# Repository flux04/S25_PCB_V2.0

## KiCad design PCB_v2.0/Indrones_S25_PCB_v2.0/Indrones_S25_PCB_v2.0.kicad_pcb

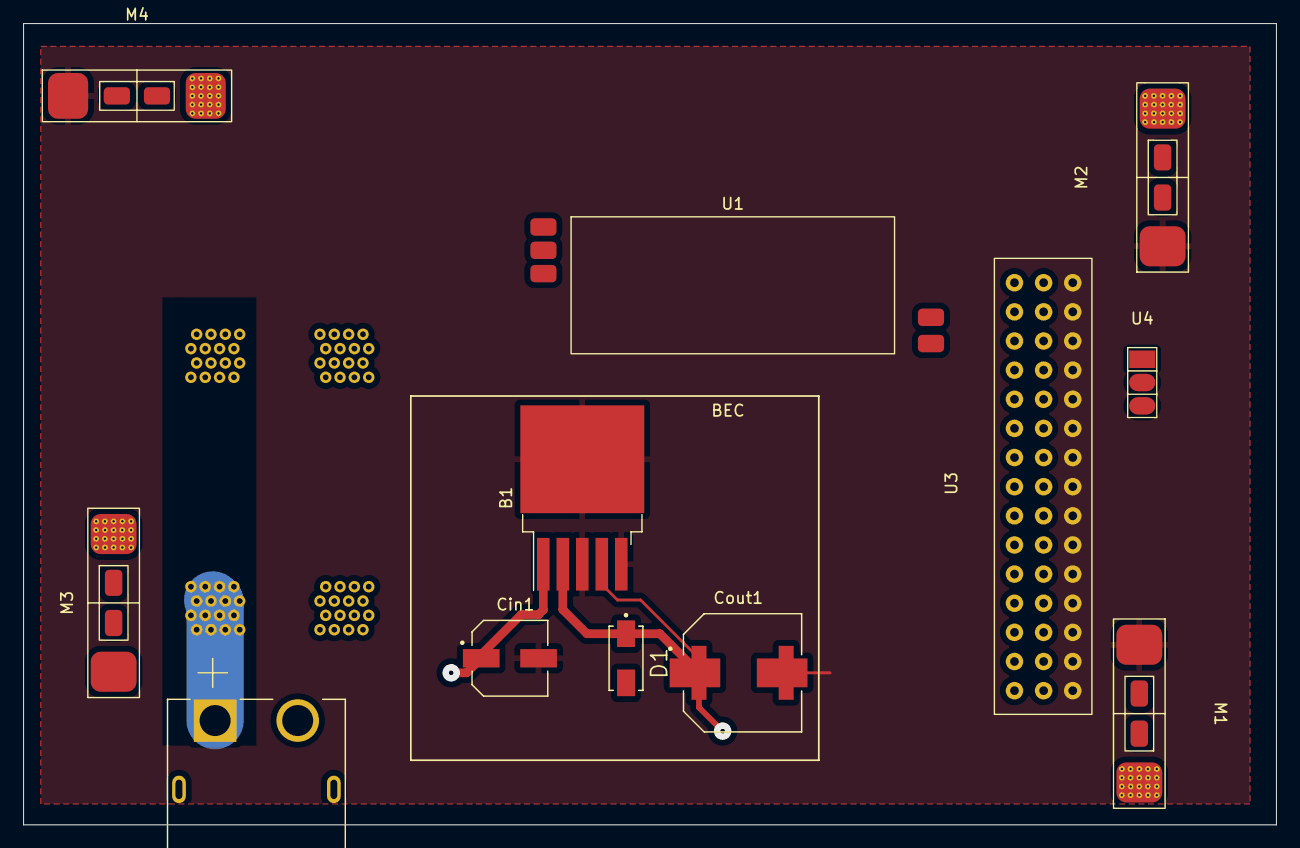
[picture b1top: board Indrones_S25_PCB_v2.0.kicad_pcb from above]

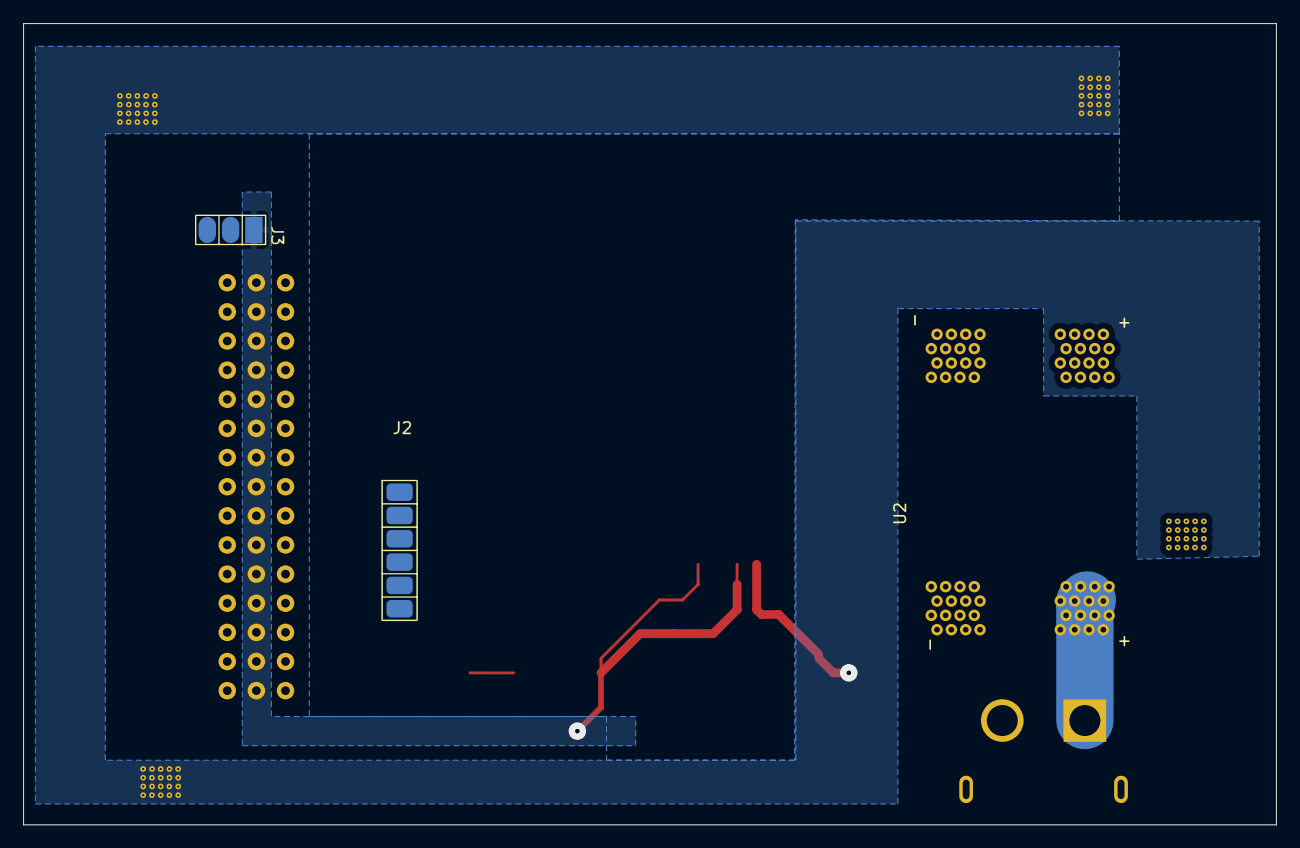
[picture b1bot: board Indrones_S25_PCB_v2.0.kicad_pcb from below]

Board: 2 copper layers, 109.2 x 69.9 mm, 15 parts (3 on the bottom side), 3 nets.

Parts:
B1: LM2576HVS-5; TO-263-5_TabPin3
Cin1: 100uF; CAP_EEEFPC101XAL
Cout1: 1000uF; CAP_EEEFK1C102SV
D1: IN5822; S1M
J1: XT60PW-M; AMASS_XT60PW-M
J2: Camera_Port; Camera
J3: PPK
M1, M2, M3, M4: Motor
U1: Relay
U2: Power_Module; Power Module
U3: 3x15_pin; 3x15_PIN
U4: RC_out; RCOut

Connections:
+5V: B1.2 (OUT), B1.4 (FB), Cout1.1, J3.1, U3.16, U3.17, U3.18, U3.19, U3.20, U3.21, U3.22, U3.23, U3.24, U3.25, U3.26, U3.27, U3.28, U3.29, U3.30
GND: B1.3 (GND), B1.5 (~ON/OFF), Cin1.2, Cout1.2, M1.-, M2.-, M4.-, U3.31, U3.32, U3.33, U3.34, U3.35, U3.36, U3.37, U3.38, U3.39, U3.40, U3.41, U3.42, U3.43, U3.44, U3.45
VCC: B1.1 (VIN), Cin1.1, M2.+, M4.+
